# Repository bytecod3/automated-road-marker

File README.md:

# automated-road-marker
Automated road marker project

## Battery sizing and component voltages 
| Component    | Voltage rating (V) | Current rating
| -------- | ------- | ------- |
| Arduino MEGA 2560  | 7-12    | -
| TT 130 accelerator/decelerator motor  | 3-6     | 170mA(at 4.5V)
| HC-SR04 ultrasonic sensor    | 5    | 4mA
|  12V Solenoid valve G1/2 DN15 BSPP Pressure Type   | 12    | 416mA
| 12V DC 385 high temperature water pump    | 12    | 400mA |
| YF-S401 Water Flow Sensor   | 5    | 15 mA (at 5V)

Recomended Battery = 12V >2000mAh

## firmware dependencies
The following libraries need to installed in Arduino 
1. LiquidCrystal I2C library by Frank de Brabander
2. I2Cdev

## Following a straight line 
The robot follows a heading that is referenced to where it starts. To do this, 
1. place the robot on the surface you want to paint
2. press the reset button WHILE THE ROBOT IS STATIONARY! There should be no movements or shaking. 
3. The robot should follow a straight heading.
4. To stop the robot, press the ON/OFF button, or disconenct the battery 

5. If using LCD, the screen should show the flow rate.

## Paint system 
The paint sequence is as follows:
1. Once the robot is turned on, it paints at intervals of 5 seconds( this can be changed in the 
code. See code!). This paint sequence produces a dotted line 
2. Pump 1, pump 2 and solenoid are turned on at the same time.
3. Flow rate is measured and displayed. 
4. Process repeats.
5. You can increase the length of the dotted line by increasing the paint interval. (Again, see code 
comments for this)

## ultrasonic designations 

US1 -> Front ultrasonic
US2 -> Right ultrasonic
US3 -> Left ultrasonic
US4 -> Resorvoir level ultrasonic

### Ultrasonic Conclusion
Ultrasonic avidance is not necesssary in the real-world. Why are you painting a road with obstacles??

## Flow meter interrupt pin change
The schematic show flow meter signal connected to pin 10. From tests, pin 10 cannot support
interrupts. Please use pin 2 for the flow meter signal.( See code on flow meter Pin -> in defines. h. If you wish 
to change the pin to pin number 3).

Only pin 2 and 3 can be used for the flow meter.

# LCD library installation
If you cannot find the Arduino-LiquidCrystal-I2C on Arduino Library manager, copy the Arduino-LiquidCrystal-I2C folder into your Arduino installation folder.
You should be able to compile the code with no errors.

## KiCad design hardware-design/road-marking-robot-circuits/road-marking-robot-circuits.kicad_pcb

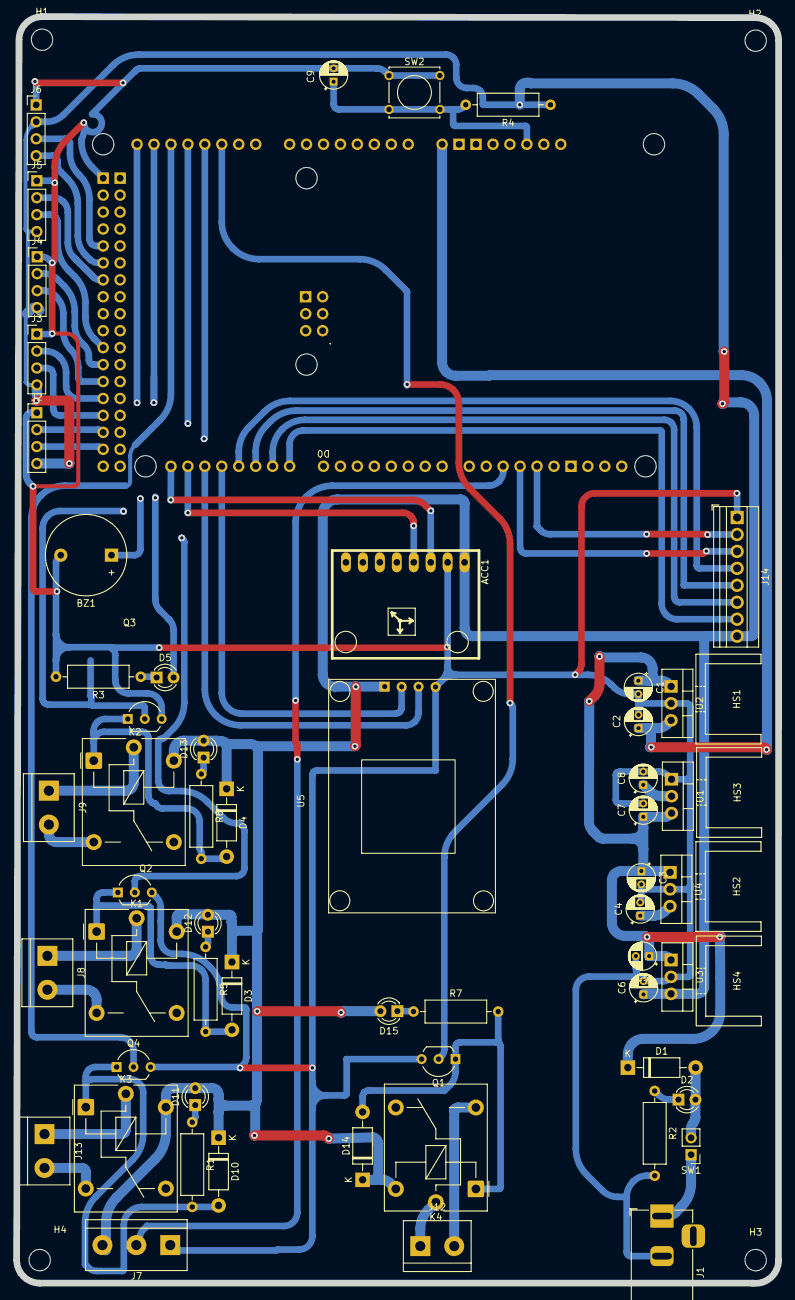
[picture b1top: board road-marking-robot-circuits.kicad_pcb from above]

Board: 2 copper layers, 114.2 x 189.8 mm, 65 parts (0 on the bottom side), 53 nets.

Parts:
A1: Arduino_Mega2560_R3_Shield
ACC1: mpu6050; GY-521
BZ1: Buzzer; Buzzer_12x9.5RM7.6
C1, C2, C3, C4, C5, C6, C7, C8: 10uf Capcaitor; CP_Radial_D4.0mm_P2.00mm
C9: 100nF; CP_Radial_D4.0mm_P2.00mm
D1, D3, D4, D10, D14: 1N4001; D_DO-41_SOD81_P10.16mm_Horizontal
D2, D5: 3mm Green LED; LED_D3.0mm
D11, D12, D13, D15: 3mm Red LED; LED_D3.0mm
H1, H2, H3, H4: MountingHole; MountingHole_3.2mm_M3
HS1, HS2, HS3, HS4: Heat sink; Heatsink_Stonecold_HS-S02_13.21x9.53mm
J1: DC Barrel Jack THT; BarrelJack_Horizontal
J2: u-sonic-1; PinHeader_1x04_P2.54mm_Vertical
J3: u-sonic-2; PinHeader_1x04_P2.54mm_Vertical
J4: u-sonic-3; PinHeader_1x04_P2.54mm_Vertical
J5: u-sonic-4; PinHeader_1x04_P2.54mm_Vertical
J6: u-sonic-5; PinHeader_1x04_P2.54mm_Vertical
J7: 3PIN Terminal block; TerminalBlock_bornier-3_P5.08mm
J8, J12, J13: 2PIN terminal block; TerminalBlock_bornier-2_P5.08mm
J9: 2 pin Terminal block; TerminalBlock_bornier-2_P5.08mm
J14: MOTOR_DRIVER; TerminalBlock_Xinya_XY308-2.54-8P_1x08_P2.54mm_Horizontal
K1, K2, K3, K4: SugarCube relay; Relay_SPDT_Finder_36.11
Q1, Q2, Q3, Q4: BC547 transistor; TO-92_Inline_Wide
R1, R2, R3, R5, R6, R7: 500R resistor; R_Axial_DIN0309_L9.0mm_D3.2mm_P12.70mm_Horizontal
R4: 10K resistor; R_Axial_DIN0309_L9.0mm_D3.2mm_P12.70mm_Horizontal
SW1: 2pin terminal block; PinHeader_1x02_P2.54mm_Vertical
SW2: push button pin; SW_Tactile_Straight_KSA0Axx1LFTR
U1: LM7909_TO220; TO-220-3_Vertical
U2: LM7812_TO220; TO-220-3_Vertical
U3: LM7805_TO220; TO-220-3_Vertical
U4: LM7806_TO220; TO-220-3_Vertical
U5: NE06M GPS Module; NEO-6M-GPS-MODULE

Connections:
5V_REG: ACC1.VCC, C6.1, D3.1 (K), D4.1 (K), D10.1 (K), D11.2 (A), D12.2 (A), D13.2 (A), D14.1 (K), D15.2 (A), J2.4, J3.4, J4.4, J5.4, J6.2, J7.3, J14.8, K1.A2, K2.A2, K3.A2, K4.A2, R4.1, U3.3 (VO), U5.1 (VCC)
6V_REG: C4.1, U4.3 (VO)
9V_REG: C8.1, U1.2 (VI)
12V_REG: A1.VIN, C2.1, U2.3 (VO)
12V_UNREG: C1.1, C3.1, C5.1, C7.1, D1.1 (K), J8.1, U1.3 (VO), U2.1 (VI), U3.1 (VI), U4.1 (VI)
/BUZZER: A1.A11, BZ1.1 (+)
/ENA: A1.D11, J14.3
/ENB: A1.D12, J14.2
/FLOW_METER: A1.D10, J7.2
/GPS_RX: A1.D18 (D18/TX1), U5.2 (RX)
/GPS_TX: A1.D19 (D19/RX1), U5.3 (TX)
/IN1: A1.D14 (D14/TX3), J14.7
/IN2: A1.D15 (D15/RX3), J14.6
/IN3: A1.D16 (D16/TX2), J14.5
/IN4: A1.D17 (D17/RX2), J14.4
/MPU_SCL: A1.D21 (D21/SCL), ACC1.SCL
/MPU_SDA: A1.D20 (D20/SDA), ACC1.SDA
/PUMP2_ACTIVATE: A1.A10, Q1.2 (B)
/PUMP_ACTIVATE: A1.A13, Q4.2 (B)
/SOLND_REL: A1.A14, Q2.2 (B)
/SPRAY_GUN_REL: A1.A15, Q3.2 (B)
/US1_EC: A1.D25, J2.2
/US1_TR: A1.D23, J2.3
/US2_EC: A1.D29, J3.2
/US2_TR: A1.D27, J3.3
/US3_EC: A1.D33, J4.2
/US3_TR: A1.D31, J4.3
/US4_EC: A1.D43, J5.2
/US4_TR: A1.D35, J5.3
/US5_EC: A1.D47, J6.3
/US5_TR: A1.D45, J6.4
/USER_LED: A1.A12, D5.2 (A)
Earth: A1.GND6 (GND), ACC1.GND, BZ1.2 (-), C1.2, C2.2, C3.2, C4.2, C5.2, C6.2, C7.2, C8.2, C9.2, J1.2, J2.1, J3.1, J4.1, J5.1, J6.1, J7.1, J14.1, K1.11, Q1.3 (E), Q2.3 (E), Q3.3 (E), Q4.3 (E), R2.2, R3.2, SW2.1, U1.1 (GND), U2.2 (GND), U3.2 (GND), U4.2 (GND), U5.4 (GND)
unnamed: A1.RST1 (RESET), C9.1, R4.2, SW2.2
unnamed: D1.2 (A), D2.2 (A), SW1.2 (B)
unnamed: D2.1 (K), R2.1
unnamed: D3.2 (A), K1.A1, Q2.1 (C), R5.2
unnamed: D4.2 (A), K2.A1, Q3.1 (C), R6.2
unnamed: D5.1 (K), R3.1
unnamed: D10.2 (A), K3.A1, Q4.1 (C), R1.2
unnamed: D11.1 (K), R1.1
unnamed: D12.1 (K), R5.1
unnamed: D13.1 (K), R6.1
unnamed: D14.2 (A), K4.A1, Q1.1 (C), R7.2
unnamed: D15.1 (K), R7.1
unnamed: J8.2, K1.14
unnamed: J9.1, K2.11
unnamed: J9.2, K2.14
unnamed: J12.1, K4.11
unnamed: J12.2, K4.14
unnamed: J13.1, K3.11
unnamed: J13.2, K3.14
unnamed: J1.1, SW1.1 (A)

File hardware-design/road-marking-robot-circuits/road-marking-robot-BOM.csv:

"#","Value","Reference","Qty","DNP"
"1","Arduino_Mega2560_R3_Shield","A1","1",""
"2","MU6060","ACC1","1",""
"3","Buzzer","BZ1","1",""
"4","10uf Capcaitor","C1,C2,C3,C4,C5,C6,C7,C8","8",""
"5","100nF","C9","1",""
"6","1N4001","D1,D3,D4,D6,D7,D8,D9,D10","8",""
"7","3mm Green LED","D2,D5","2",""
"8","3mm Red LED","D11,D12,D13","3",""
"9","Heat sink","HS1,HS2,HS3,HS4","4",""
"10","DC Barrel Jack THT","J1","1",""
"11","u-sonic-1","J2","1",""
"12","u-sonic-2","J3","1",""
"13","u-sonic-3","J4","1",""
"14","u-sonic-4","J5","1",""
"15","u-sonic-5","J6","1",""
"16","3PIN Terminal block","J7","1",""
"17","2PIN terminal block","J8,J11,J13","3",""
"18","2 pin Terminal block","J9","1",""
"19","2 PIN terminal Block","J10","1",""
"20","SugarCube relay","K1,K2,K3","3",""
"21","ROBOT_WHEEL","M2","1","DNP"
"22","BC547 transistor","Q2,Q3,Q4","3",""
"23","500R resistor","R1,R2,R3,R5,R6","5",""
"24","10K resistor","R4","1",""
"25","2pin terminal block","SW1","1",""
"26","push button pin","SW2","1",""
"27","LM7909_TO220","U1","1",""
"28","LM7812_TO220","U2","1",""
"29","LM7805_TO220","U3","1",""
"30","LM7806_TO220","U4","1",""
"31","NE06M GPS Module","U5","1",""
"32","L293D Motor driver chip","U6","1",""

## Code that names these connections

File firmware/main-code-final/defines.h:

#ifndef DEFINES_H
#define DEFINES_H

#define debug(x) Serial.print(x)
#define debugln(x) Serial.println(x)


#define BUZZER A11
#define USER_LED A12


// MOTOR DRIVER PINS
#define ENA 11
#define ENB 12
#define IN1 14
#define IN2 15
#define IN3 16
#define IN4 17

// paint system pins
#define PUMP_ONE_RELAY_PIN        A13
#define PUMP_TWO_RELAY_PIN        A10
#define SOLENOID_VALVE_RELAY_PIN  A14
#define FLOW_PIN 2 // flow meter pin


#endif

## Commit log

2024-11-21 initilizes project structure
2024-11-30 adds motor driver
2024-11-30 first good build
2024-11-30 adds battery estimation
2025-02-13 [ADDS] power supply
2025-02-13 [ADDS] solenoid valve relay
2025-02-24 adds footprints
2025-02-24 [UPDATES] arduino position
2025-02-24 [UPDATES] PCB design
2025-04-01 updates FIRMWARE for ARDUINO
2025-04-06 [ADDS] yaw calculation
2025-05-04 adds motor control code
2025-05-10 ADDS z axis offset error
2025-05-10 ADDS Yaw angle measurement
2025-05-11 ADDS left right motor
2025-05-11 FIXES the paint system
2025-05-11 UPDATES README.md
2025-05-11 ADDS working code WITHOUT ULTRASONIC
